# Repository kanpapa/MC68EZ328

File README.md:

# MC68EZ328 DragonOne SBC

We are designing the MC68EZ328 DragonOne SBC with KiCad.

Based on DragonOne V1.0 (C) Khaled Hassounah  
http://www.mediumware.net/DragonOne/DragonOne.htm  

## Spec

* CPU: MC68EZ328 DragonBall-EZ
* Flash Memory: Am29LV033C 32 Megabit (4M x 8-Bit) x 2
* DRAM: MT4LC4M16R6 64 Megabit (4M x 16-bit)
* RTC: DS1306

## Repository Contents

* /b/
  * All b-record for programming and testing the MC68EZ328 DragonOne.
* /bbug/
  * BBUG: a bootstrap mode debugger. Implementation of BBUG using python3 and pyserial.
* /d/
  * This is the data to execute a series of commands in 68k-Monitor.  
* /Hardware/
  * PDF files of schematics and BOMs
* /KiCad/
  * PCB design data and Gerber data for [KiCad](https://www.kicad.org/).
* /Pictues/
  * some pictures
* /src
  * All Source Code for Flash Programming and test programming. The assembler uses [EASy68K](http://www.easy68k.com/).

## How to install uClinux for the DragonOne SBC

[How to install uClinux](/uClinux-build2flash_en.md)  

See below for the uClinux source code and tools for the MC68EZ328 DragonOne SBC.  
https://github.com/kanpapa/uClinux-dist-20020220  
https://github.com/kanpapa/m68k-elf-tools  

## Blog

You can also refer to my blog. (in Japanese)    
https://kanpapa.com/today/electronics/microcomputer/mc68ez328/

## Pictures

MC68EZ328 CPU  

CPU board Rev. 0.3 PCB image  

LAN board Rev. 0.2 PCB image  

Running uClinux  

Running Network!  

## License Information

This code is public domain under the BSD-3-Clause License.  
Copyright (c) 2021, Kazuhiro Ouchi  
All rights reserved.  

References to any products, programs or services do not imply that they will be available in all countries in which their respective owner operates.

Company, product, or services names may be trademarks or services marks of others.

All libraries used in this code are copyright their respective authors.

68k-Monitor Copyright (c) 2015, Hayden Kroepfl

The DragonOne Microcomputer hardware design Copyright (C) Khaled Hassounah

Many thanks to the original authors for making their designs and code avaialble as open source.

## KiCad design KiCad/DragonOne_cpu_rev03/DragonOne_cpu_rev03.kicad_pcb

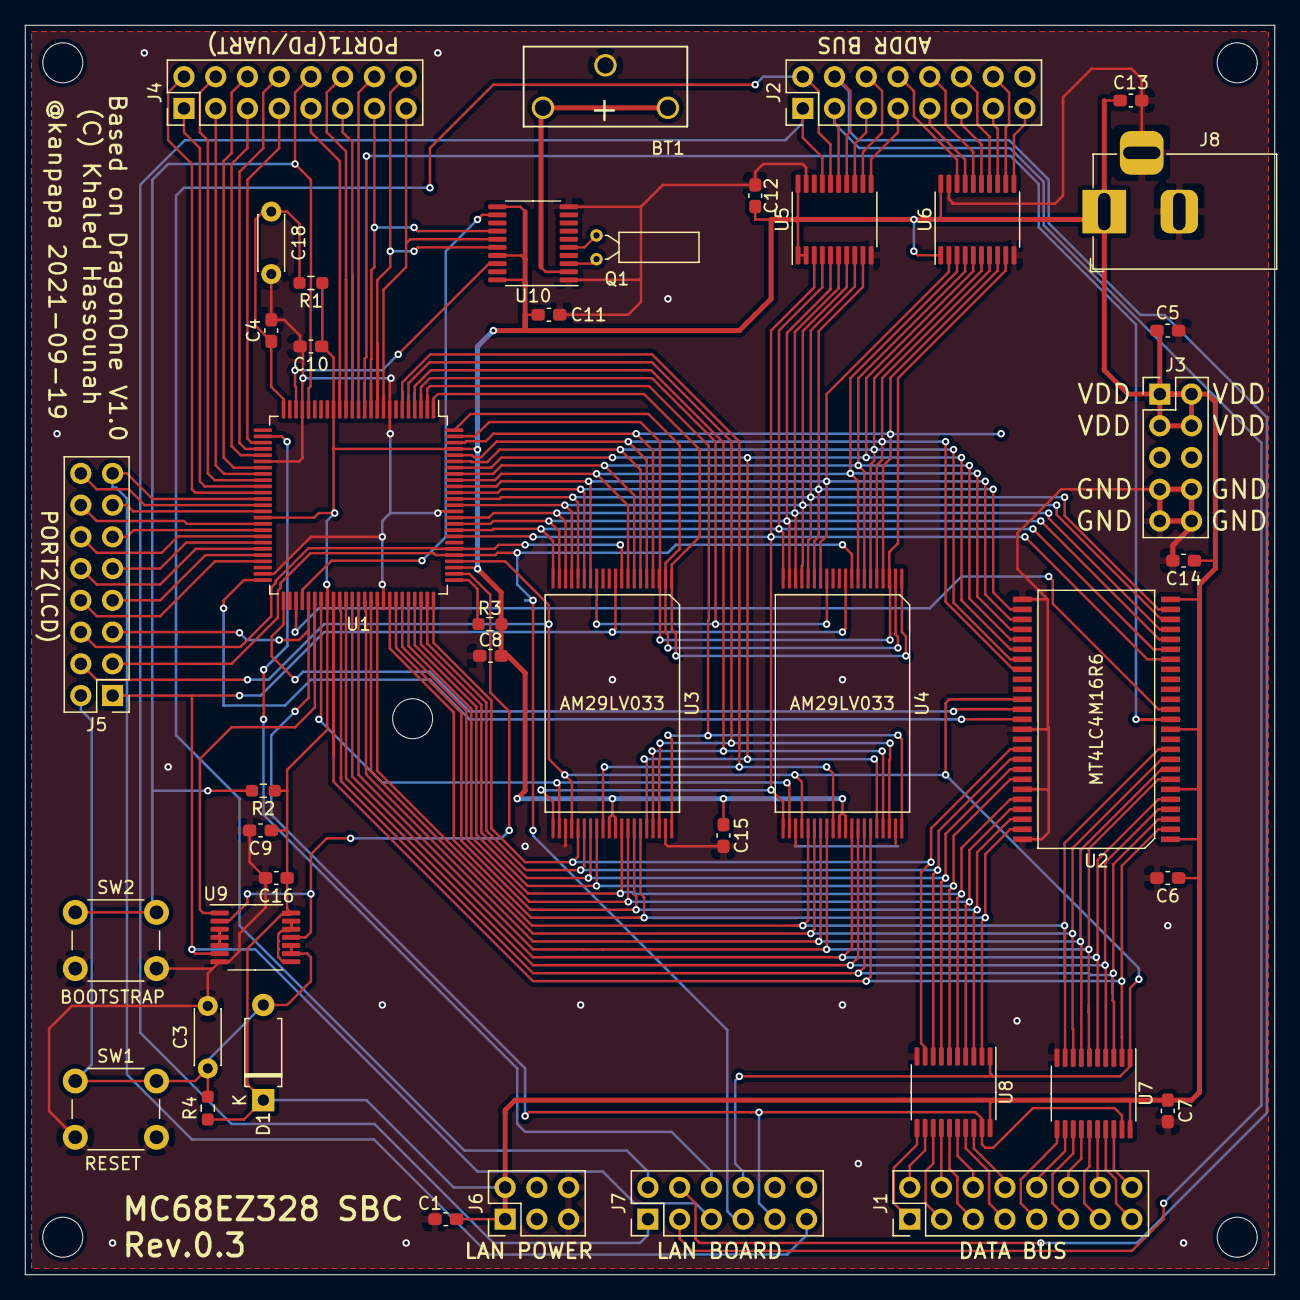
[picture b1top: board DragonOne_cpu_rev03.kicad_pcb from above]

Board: 2 copper layers, 100.0 x 100.0 mm, 48 parts (0 on the bottom side), 120 nets.

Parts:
BT1: 3V; CH74-2032LF
C1, C4, C5, C6, C7, C8, C9, C10, C11, C12, C13, C14, C15, C16: 0.1uf; C_0603_1608Metric_Pad1.08x0.95mm_HandSolder
C3, C18: 2.2uf; C_Disc_D4.3mm_W1.9mm_P5.00mm
D1: 1N4148; D_A-405_P7.62mm_Horizontal
J1: DATA_BUS; PinHeader_2x08_P2.54mm_Vertical
J2: ADDR_BUS; PinHeader_2x08_P2.54mm_Vertical
J3: POWER; PinHeader_2x05_P2.54mm_Vertical
J4: PORT1; PinHeader_2x08_P2.54mm_Vertical
J5: PORT2; PinHeader_2x08_P2.54mm_Vertical
J6: LAN POWER; PinHeader_2x03_P2.54mm_Vertical
J7: LAN CONTROL; PinHeader_2x06_P2.54mm_Vertical
J8: Barrel_Jack_Switch; BarrelJack_Horizontal
MH1, MH2, MH3, MH4, MH5: MountingHole_3.2mm_M3
Q1: 32.768kHz; Crystal_DS26_D2.0mm_L6.0mm_Horizontal
R1: 430; R_0603_1608Metric_Pad0.98x0.95mm_HandSolder
R2, R3: 3.3K; R_0603_1608Metric_Pad0.98x0.95mm_HandSolder
R4: 3.3k; R_0603_1608Metric_Pad0.98x0.95mm_HandSolder
SW1: RESET; SW_PUSH_6mm
SW2: BOOTSTRAP; SW_PUSH_6mm
U1: MC68EZ328; TQFP-100_14x14mm_P0.5mm
U2: MT4LC4M16R6; TSOP-II-50_21x10.16mm_P0.8mm
U3, U4: AM29LV033; TSOP-I-40_18.4x10mm_P0.5mm
U5, U6, U7, U8: 74LCX245; TSSOP-20_4.4x6.5mm_P0.65mm
U9: 74LCX00; TSSOP-14_4.4x5mm_P0.65mm
U10: DS1306; TSSOP-20_4.4x6.5mm_P0.65mm

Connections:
/A1: U1.83, U2.19, U3.21, U4.21, U5.3
/A2: U1.84, U2.20, U3.20, U4.20, U5.4
/A3: U1.85, U2.21, U3.19, U4.19, U5.5
/A4: U1.86, U2.22, U3.18, U4.18, U5.6
/A5: U1.88, U2.23, U3.17, U4.17, U5.7
/A6: U1.89, U2.24, U3.16, U4.16, U5.8
/A7: U1.90, U2.27, U3.15, U4.15, U5.9
/A8: U1.91, U2.28, U3.14, U4.14, U6.2
/A9: U1.92, U2.29, U3.8, U4.8, U6.3
/A10: U1.93, U2.30, U3.7, U4.7, U6.4
/A11: U1.94, U2.31, U3.36, U4.36, U6.5
/A12: U1.95, U2.32, U3.6, U4.6, U6.6
/A13: U1.96, U2.33, U3.5, U4.5, U6.7
/A14: U1.98, U3.4, U4.4, U6.8
/A15: U1.99, U3.3, U4.3, U6.9
/A16: U1.100, U3.2, U4.2
/A17: U1.1, U3.1, U4.1
/A18: U1.2, U3.40, U4.40
/A19: U1.3, U3.13, U4.13
/A20: U1.4, U3.37, U4.37
/A21: U1.5, U3.38, U4.38
/A22: U1.6, U3.29, U4.29
/AB1: J2.1, J7.1, U5.17
/AB2: J2.2, J7.2, U5.16
/AB3: J2.3, J7.3, U5.15
/AB4: J2.4, J7.4, U5.14
/AB5: J2.5, U5.13
/AB6: J2.6, U5.12
/AB7: J2.7, U5.11
/AB8: J2.8, U6.18
/AB9: J2.9, U6.17
/AB10: J2.10, U6.16
/AB11: J2.11, U6.15
/AB12: J2.12, U6.14
/AB13: J2.13, U6.13
/AB14: J2.14, U6.12
/AB15: J2.15, U6.11
/CLOCK: U1.23, U10.18
/D0: U1.75, U2.41, U3.25, U8.9
/D1: U1.74, U2.42, U3.26, U8.8
/D2: U1.73, U2.43, U3.27, U8.7
/D3: U1.72, U2.44, U3.28, U8.6
/D4: U1.71, U2.46, U3.32, U8.5
/D5: U1.70, U2.47, U3.33, U8.4
/D6: U1.69, U2.48, U3.34, U8.3
/D7: U1.68, U2.49, U3.35, U8.2
/D8: U1.66, U2.10, U4.25, U7.9
/D9: U1.65, U2.9, U4.26, U7.8
/D10: U1.64, U2.8, U4.27, U7.7
/D11: U1.63, U2.7, U4.28, U7.6
/D12: U1.62, U2.5, U4.32, U7.5
/D13: U1.61, U2.4, U4.33, U7.4
/D14: U1.60, U2.3, U4.34, U7.3
/D15: U1.59, U2.2, U4.35, U7.2
/DB0: J1.1, U8.11
/DB1: J1.2, U8.12
/DB2: J1.3, U8.13
/DB3: J1.4, U8.14
/DB4: J1.5, U8.15
/DB5: J1.6, U8.16
/DB6: J1.7, U8.17
/DB7: J1.8, U8.18
/DB8: J1.9, U7.11
/DB9: J1.10, U7.12
/DB10: J1.11, U7.13
/DB11: J1.12, U7.14
/DB12: J1.13, U7.15
/DB13: J1.14, U7.16
/DB14: J1.15, U7.17
/DB15: J1.16, U7.18
/LACD: J5.16, U1.38
/LCLK: J5.13, U1.39
/LCON: J5.15, J7.11, U1.37
/LD0: J5.7, U1.46
/LD1: J5.10, U1.45
/LD2: J5.9, U1.44
/LD3: J5.12, U1.43
/LFLM: J5.11, U1.42
/LLP: J5.14, U1.41
/PD0: J4.2, U1.36
/PD1: J4.1, U1.35
/PD2: J4.4, U1.34
/PD3: J4.3, U1.33
/PD4: J4.6, U1.32
/PD5: J4.5, U1.30
/PD6: J4.8, U1.29
/PD7: J4.7, U1.28
/PWM0: J5.8, U1.47
/RXD: J4.14, U1.13
/SCLK: J4.13, U1.11, U10.14
/SRXD: J4.16, U1.10, U10.16
/STXD: J4.15, U1.9, U10.15
/TIME: U1.54, U10.12
/TXD: J4.11, U1.14
/~BDM: J4.10, R2.2, SW2.1, U1.21
/~CAS0: U1.51, U2.37
/~CAS1: U1.50, U2.38
/~CSA0: U1.57, U3.22, U4.22
/~CTS: J4.9, U1.16
/~DWE: U1.12, U2.13
/~EXTRN: J5.5, J7.9, U1.55, U7.19, U8.19
/~IRQ5: J7.6, U1.27
/~LWE: J5.6, U1.81, U3.9
/~PRSET: U1.77, U9.2, U9.11
/~RAS0: U1.53, U2.14
/~RD: J5.4, J7.8, U1.79, U2.36, U3.24, U4.24, U7.1, U8.1
/~RESET: J5.1, J7.5, U3.10, U4.10, U9.6
/~RTS: J4.12, U1.15
/~SRSET: U1.56, U9.1
/~UWE: J5.3, J7.7, U1.80, U4.9
/~XRSET: C3.1, D1.2, J5.2, R4.2, SW1.1, U9.9, U9.10
GND: BT1.2, C1.2, C3.2, C4.2, C5.2, C6.2, C7.2, C8.2, C9.2, C10.2, C11.2, C12.2, C13.2, C14.2, C15.2, C16.2, C18.2, J3.7, J3.8, J3.9, J3.10, J6.5, J6.6, J8.2, J8.3, SW1.2, SW2.2, U1.8, U1.22, U1.31, U1.49, U1.67, U1.87, U2.26, U2.39, U2.45, U2.50, U3.23, U3.39, U4.23, U4.39, U5.10, U5.19, U6.10, U6.19, U7.10, U8.10, U9.7, U10.1, U10.10
unnamed: BT1.1, U10.2
unnamed: C4.1, C18.1, R1.2, U1.25
unnamed: Q1.1, U10.3
unnamed: Q1.2, U10.5
unnamed: R3.2, U1.76
unnamed: U9.3, U9.4, U9.5
unnamed: U9.8, U9.12, U9.13
VDD: C1.1, C5.1, C6.1, C7.1, C8.1, C9.1, C10.1, C11.1, C12.1, C13.1, C14.1, C15.1, C16.1, D1.1, J3.1, J3.2, J3.3, J3.4, J6.1, J6.2, J8.1, R1.1, R2.1, R3.1, R4.1, U1.17, U1.40, U1.58, U1.78, U1.97, U2.1, U2.6, U2.12, U2.25, U3.30, U3.31, U4.30, U4.31, U5.1, U5.2, U5.20, U6.1, U6.20, U7.20, U8.20, U9.14, U10.11, U10.17, U10.20

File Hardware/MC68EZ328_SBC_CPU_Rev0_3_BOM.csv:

Reference,Quantity,Value,Footprint,販売店（参考）,型番,URL,備考
BT1,1,3V,DragonOne_rev00:CH74-2032LF,秋月電子,ボタン電池基板取付用ホルダーＣＲ２０３２用（縦・小型）[CH74-2032LF][P-01443]1個 ￥50(税込),https://akizukidenshi.com/catalog/g/gP-01443/,
C3 C18,2,2.2uf,Capacitor_THT:C_Disc_D4.3mm_W1.9mm_P5.00mm,秋月電子,積層セラミックコンデンサー２．２μＦ５０Ｖ　Ｘ７Ｒ　５ｍｍ[RDER71H225K2K1H03B][P-08152]1個 ￥25(税込),https://akizukidenshi.com/catalog/g/gP-08152/,
C1 C4 C5 C6 C7 C8 C9 C10 C11 C12 C13 C14 C15 C16,14,0.1uf,Capacitor_SMD:C_0603_1608Metric_Pad1.08x0.95mm_HandSolder,秋月電子,太陽誘電チップ積層セラミックコンデンサー０．１μＦ２５Ｖ　Ｆ／Ｙ５Ｖ　１６０８　（１００個入）[TMK107F104ZZ-T][P-13071]1パック ￥100,https://www.akizukidenshi.com/catalog/g/gP-13071/,
D1,1,1N4148,Diode_THT:D_A-405_P10.16mm_Horizontal,秋月電子,汎用小信号高速スイッチング・ダイオード１Ｎ４１４８　１００Ｖ２００ｍＡ（５０本入）[1N4148][I-00941]1パック ￥100(税込),https://akizukidenshi.com/catalog/g/gI-00941/,
J1,1,DATA_BUS,Connector_PinHeader_2.54mm:PinHeader_2x08_P2.54mm_Vertical,秋月電子,ピンヘッダ２×８,https://akizukidenshi.com/catalog/g/gC-00082/,"ピンヘッダ２×４０（８０Ｐ）[PH-2x40SG][C-00082]1本￥50(税込)を折って使う"
J2,1,ADDR_BUS,Connector_PinHeader_2.54mm:PinHeader_2x08_P2.54mm_Vertical,秋月電子,ピンヘッダ２×８,,
J3,1,POWER,Connector_PinHeader_2.54mm:PinHeader_2x05_P2.54mm_Vertical,秋月電子,ピンヘッダ２×５,,
J4,1,PORT1,Connector_PinHeader_2.54mm:PinHeader_2x08_P2.54mm_Vertical,秋月電子,ピンヘッダ２×８,,
J5,1,PORT2,Connector_PinHeader_2.54mm:PinHeader_2x08_P2.54mm_Vertical,秋月電子,ピンヘッダ２×８,,
J6,1,LAN POWER,Connector_PinHeader_2.54mm:PinHeader_2x03_P2.54mm_Vertical,秋月電子,ピンヘッダ２×３,,
J7,1,LAN BOARD,Connector_PinHeader_2.54mm:PinHeader_2x06_P2.54mm_Vertical,秋月電子,ピンヘッダ２×６,,
J8,1,POWER,Cobbector_BarrelJack:BarrelJack_Horizontal,秋月電子,２．１ｍｍ標準ＤＣジャック基板取付用　ＭＪ－１７９Ｐ[MJ-179P][C-00077]1個 ￥40(税込),https://www.akizukidenshi.com/catalog/g/gC-00077/,
Q1,1,32.768kHz,Crystal:Crystal_AT310_D3.0mm_L10.0mm_Horizontal,秋月電子,"クリスタル（水晶発振子）32.768KHz[VT-200-F 32.768kHz][P-04005]1個 ￥30(税込)",https://akizukidenshi.com/catalog/g/gP-04005/,
R1,1,430Ω,Resistor_SMD:R_0603_1608Metric_Pad0.98x0.95mm_HandSolder,"千石電商日米商事共立エレショップ",チップ抵抗１／１０Ｗ４３０Ω ０６０３ １６０８,,
R2 R3 R4,3,3.3K,Resistor_SMD:R_0603_1608Metric_Pad0.98x0.95mm_HandSolder,"千石電商日米商事秋月電子共立エレショップ",チップ抵抗１／１０Ｗ３．３ｋΩ　０６０３　１６０８,https://www.akizukidenshi.com/catalog/g/gR-14661/,
SW1,1,RESET,Button_Switch_THT:SW_PUSH_6mm,秋月電子,タクトスイッチ（オレンジ色）[TS-0606-F-N-ORG][P-03652]1個 ￥10(税込),https://akizukidenshi.com/catalog/g/gP-03652/,
SW2,1,BOOTSTRAP,Button_Switch_THT:SW_PUSH_6mm,秋月電子,タクトスイッチ（白色）[TS-0606-F-N-WHT][P-03648]1個 ￥10(税込),https://akizukidenshi.com/catalog/g/gP-03648/,色はおこのみで
U1,1,MC68EZ328,Package_QFP:TQFP-100_14x14mm_P0.5mm,AliExpress、eBay,,,
U10,1,DS1306,Package_SO:TSSOP-20_4.4x6.5mm_P0.65mm,AliExpress、eBay,,,
U2,1,MT4LC4M16R6,DragonOne_rev00:TSOP-II-50_21x10.16mm_P0.8mm,AliExpress、eBay,,,
U3 U4,2,AM29LV033,DragonOne_rev00:TSOP-I-40_18.4x10mm_P0.5mm,AliExpress、eBay,,,
U5 U6 U7 U8,4,74LCX245,Package_SO:TSSOP-20_4.4x6.5mm_P0.65mm,秋月電子,８ビットバストランシーバ３ステート出力７４ＬＣＸ２４５ＦＴ（５個入）[74LCX245FT(AJ)][I-14111]1パック ￥130(税込),https://akizukidenshi.com/catalog/g/gI-14111/,
U9,1,74LCX00,Package_SO:TSSOP-14_4.4x5mm_P0.65mm,秋月電子,４回路２入力ＮＡＮＤ７４ＬＣＸ００ＦＴ（５個入）[74LCX00FT(AJ)][I-14106]1パック ￥100(税込),https://akizukidenshi.com/catalog/g/gI-14106/,

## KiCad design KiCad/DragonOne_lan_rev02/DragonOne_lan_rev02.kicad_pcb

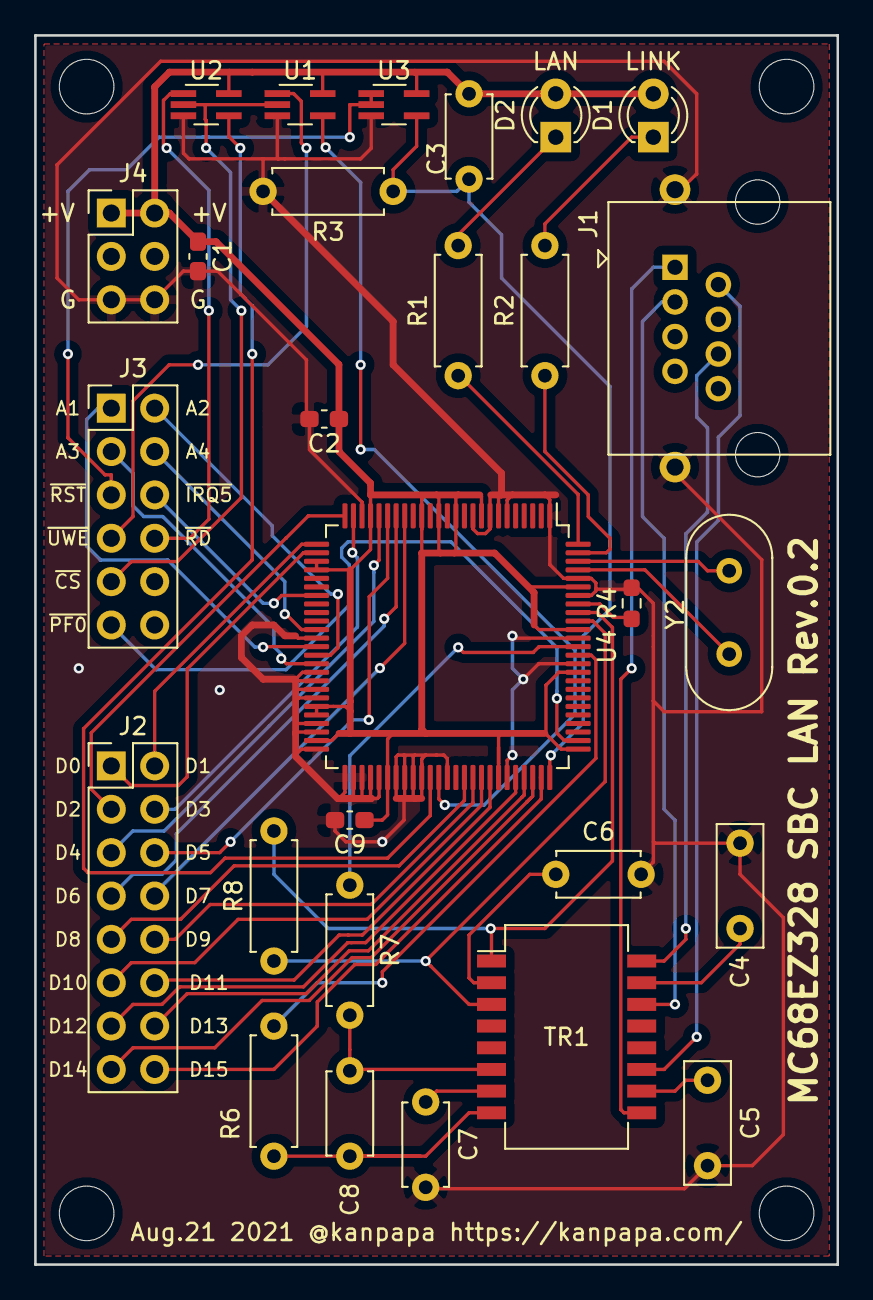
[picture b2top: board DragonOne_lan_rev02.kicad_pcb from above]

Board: 2 copper layers, 47.0 x 72.0 mm, 32 parts (0 on the bottom side), 52 nets.

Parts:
C1, C2, C9: 0.1uF; C_0603_1608Metric_Pad1.08x0.95mm_HandSolder
C3, C6, C7: 0.1uF; C_Disc_D4.7mm_W2.5mm_P5.00mm
C4: 4700pF/1kV; C_Disc_D7.0mm_W2.5mm_P5.00mm
C5: 4700pF/1KV; C_Disc_D7.0mm_W2.5mm_P5.00mm
C8: 560pF; C_Disc_D4.7mm_W2.5mm_P5.00mm
D1: LINK LED; LED_D3.0mm
D2: LAN LED; LED_D3.0mm
J1: 8P8C_Shielded; RJ45_Akizuki_7810-8P8C
J2: DATA_BUS; PinHeader_2x08_P2.54mm_Vertical
J3: CTRL_BUS; PinHeader_2x06_P2.54mm_Vertical
J4: PWR; PinHeader_2x03_P2.54mm_Vertical
MH1, MH2, MH3, MH4: MountingHole_3.2mm_M3
R1, R2: 560; R_Axial_DIN0207_L6.3mm_D2.5mm_P7.62mm_Horizontal
R3: 100K; R_Axial_DIN0207_L6.3mm_D2.5mm_P7.62mm_Horizontal
R4: 4.99K 1%; R_0603_1608Metric_Pad0.98x0.95mm_HandSolder
R6, R7: 8.2 1%; R_Axial_DIN0207_L6.3mm_D2.5mm_P7.62mm_Horizontal
R8: 100, 1%; R_Axial_DIN0207_L6.3mm_D2.5mm_P7.62mm_Horizontal
TR1: E2023EL; Transformer_Ethernet_Bourns_PT61017PEL
U1, U2: TC7S32FU; SOT-353_SC-70-5_Handsoldering
U3: TC7SH00FU; SOT-353_SC-70-5_Handsoldering
U4: CS8900A-CQ3Z; TQFP-100_14x14mm_P0.5mm
Y2: 20MHz; Crystal_HC49-4H_Vertical

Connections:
/AB1: J3.1, U4.38
/AB2: J3.2, U4.39
/AB3: J3.3, U4.40
/AB4: J3.4, U4.36
/DB0: J2.1, U4.27
/DB1: J2.2, U4.26
/DB2: J2.3, U4.25
/DB3: J2.4, U4.24
/DB4: J2.5, U4.21
/DB5: J2.6, U4.20
/DB6: J2.7, U4.19
/DB7: J2.8, U4.18
/DB8: J2.9, U4.65
/DB9: J2.10, U4.66
/DB10: J2.11, U4.67
/DB11: J2.12, U4.68
/DB12: J2.13, U4.71
/DB13: J2.14, U4.72
/DB14: J2.15, U4.73
/DB15: J2.16, U4.74
/PF0: J3.11, U4.77
/RD+: J1.3, TR1.14
/RD-: J1.6, TR1.16
/RXD+: R8.1, TR1.3, U4.91
/RXD-: R8.2, TR1.1, U4.92
/TD+: J1.1, TR1.9
/TD-: J1.2, TR1.11
/TXD+: C8.1, R6.2, TR1.8
/TXD-: C8.2, R7.2, TR1.6
/~CSB0: J3.9, U1.2, U2.2
/~IRQ5: J3.6, U4.32
/~RD: J3.8, U2.1
/~RESET: J3.5, U3.1, U3.2
/~UWE: J3.7, U1.1
GND: C1.2, C2.2, C4.2, C5.2, C6.2, C7.2, C9.2, J1.SH, J4.5, J4.6, R3.2, R4.2, U1.3, U2.3, U3.3, U4.1, U4.6, U4.7, U4.8, U4.10, U4.23, U4.37, U4.41, U4.42, U4.43, U4.44, U4.47, U4.48, U4.50, U4.51, U4.52, U4.53, U4.54, U4.55, U4.57, U4.58, U4.59, U4.60, U4.63, U4.70, U4.86, U4.89, U4.94, U4.96
unnamed: C3.2, R3.1, U3.4, U4.75
unnamed: C4.1, TR1.15
unnamed: C5.1, TR1.10
unnamed: C6.1, TR1.2
unnamed: C7.1, TR1.7
unnamed: D1.1, R2.2
unnamed: D2.1, R1.2
unnamed: R1.1, U4.100
unnamed: R2.1, U4.99
unnamed: R4.1, U4.93
unnamed: R6.1, U4.87
unnamed: R7.1, U4.88
unnamed: U1.4, U4.62
unnamed: U2.4, U4.61
unnamed: U4.97, Y2.2
unnamed: U4.98, Y2.1
VCC: C1.1, C2.1, C3.1, C9.1, D1.2, D2.2, J4.1, J4.2, U1.5, U2.5, U3.5, U4.9, U4.12, U4.14, U4.16, U4.22, U4.28, U4.29, U4.45, U4.46, U4.49, U4.56, U4.69, U4.76, U4.85, U4.90, U4.95

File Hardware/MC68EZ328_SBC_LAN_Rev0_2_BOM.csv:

Reference,Quantity,Value,販売店（参考）,型番,URL,備考
C1 C2 C9,3,0.1uF,秋月電子,太陽誘電チップ積層セラミックコンデンサー０．１μＦ２５Ｖ　Ｆ／Ｙ５Ｖ　１６０８　（１００個入）[TMK107F104ZZ-T][P-13071]1パック ￥100(税込),https://akizukidenshi.com/catalog/g/gP-13071/,
C4 C5,2,4700pF/1kV,マルツ,セラミックコンデンサー 4700pF【CY5P472K1K12D】パッケージ：・静電容量：4700pF・定格電圧：1kVDC・容量許容差：±10％・リードピッチ：5mm,https://www.marutsu.co.jp/GoodsDetail.jsp?q=CY5P472K&salesGo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,
C3 C6 C7,3,0.1uF,秋月電子,"リード型積層セラミックコンデンサー０．１μＦ５０Ｖ　Ｆ　５ｍｍピッチ　（１０個入）[RPEF11H104Z2M1A01A][P-00340]1テープ ￥100(税込)",https://akizukidenshi.com/catalog/g/gP-00340/,
C8,1,560pF,秋月電子,"絶縁ラジアルリード型積層セラミックコンデンサー５６０ｐＦ５０Ｖ５ｍｍ（１０個入）[RDE5C1H561J0K1H03B][P-08111]1パック ￥100(税込)",https://akizukidenshi.com/catalog/g/gP-08111/,
D1,1,LINK LED,aitendo,,,
D2,1,LAN LED,aitendo,,,
IC1,1,CS8900A-CQ3Z,AliExpress,,,
J1,1,LAN_CON,秋月電子,基板取付用ＬＡＮコネクタ（モジュラージャック）（ＲＪ－４５）[7810-8P8C][C-00159]1個 ￥100(税込),https://akizukidenshi.com/catalog/g/gC-00159/,
J2,1,DATA_BUS,秋月電子,ピンヘッダ２×４０（８０Ｐ）[PH-2x40SG][C-00082]1本 ￥50(税込),https://akizukidenshi.com/catalog/g/gC-00082/,折って使う
J3,1,CTRL_BUS,秋月電子,ピンヘッダ２×４０（８０Ｐ）[PH-2x40SG][C-00082]1本 ￥50(税込),https://akizukidenshi.com/catalog/g/gC-00082/,折って使う
J4,1,PWR,秋月電子,ピンヘッダ２×３（６Ｐ）[PH-2x3SG][C-15825]1本 ￥10(税込) 数割有,https://akizukidenshi.com/catalog/g/gC-15825/,
R1 R2,2,560Ω,千石電商,カーボン抵抗 1/4W 560Ω±5% RD25J 560Ω,,
R3,1,100K,千石電商,カーボン抵抗 1/4W 100KΩ±5% RD25J 100KΩ,,
R4,1,4.99K 1%,秋月電子,"超精密級 金属皮膜チップ抵抗器　１６０８　１／１０Ｗ４．９９ｋΩ０．１％（５個入）[RG1608N-4991B-T5][R-11794]1パック ￥100(税込)",https://akizukidenshi.com/catalog/g/gR-11794/,
R6 R7,2,8.2 1%,千石電商,金属被膜抵抗器 1/4W 8.2Ω±1% RLC25FX 8.2Ω,,
R8,1,"100, 1%",千石電商,金属被膜抵抗器 1/4W 100Ω±1% RLC25FY 100Ω,,
TR1,1,E2023EL,"マルツ, AliExpress",,,
U1 U2,2,TC7S32FU,秋月電子,２入力ＯＲゲートＴＣ７Ｓ３２ＦＵ（５個入）[TC7S32FU][I-10465]1パック ￥150(税込),https://akizukidenshi.com/catalog/g/gI-10465/,
U3,1,TC7SH00FU,秋月電子,２入力ＮＡＮＤ ＴＣ７ＳＨ００ＦＵ（１０個入）[TC7SH00FULJ(CB][I-15748]1パック ￥100(税込),https://akizukidenshi.com/catalog/g/gI-15748/,
Y2,1,20MHz,秋月電子,クリスタル（水晶発振子）２０ＭＨｚ[HUSG-20.000-20][P-08673]1個 ￥30(税込),https://akizukidenshi.com/catalog/g/gP-08673/,

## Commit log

2021-03-16 1st commit
2021-03-16 Added spec
2021-03-16 Update spec
2021-03-20 Added 2flash-kh and pictures
2021-03-20 Added DragonOne Site URL
2021-03-20 Added CR
2021-03-20 Added pictures
2021-03-20 Added bbug teraterm macro version
2021-03-20 Update bbug
2021-04-10 Fixed for my development environment.
2021-04-10 Added usage in Japanese.
2021-04-10 Fixed typo
2021-04-14 Added repository contents
2021-04-19 Added mdisp.ttl
2021-04-21 1st release
2021-04-22 update indent
2021-04-22 Added initb.py
2021-04-23 Added loadb, start
2021-04-24 Fixed bug
2021-04-24 Updated serialport for macos
2021-04-24 Added schematic
2021-04-25 Updated schematic
2021-04-25 Updated contents list
2021-05-01 Added init.b
2021-05-01 Fixed blank
2021-05-01 Added init.py
2021-05-01 Added stob.py
2021-05-02 Added Monitor.b
2021-05-02 Updated LF code
2021-05-02 Added helloworld.x68
2021-05-02 Added helloworld
2021-05-02 Added echoback
2021-05-03 Updated 32bit address display
2021-05-03 Added flashtools alpha
2021-05-04 Added gitignore
2021-05-04 Updated flashtools src
2021-05-04 Update flashtools
2021-05-05 Update flashtools alpha (erase and program, reset)
2021-05-06 Updated flashtools.x68
2021-05-06 updated flashtools
2021-05-06 Updated flashtools beta version
2021-05-08 Added flashtools_monitor.b
2021-05-08 Fixed line end code
2021-05-08 Fixed S3 address
2021-05-08 Added license information
2021-05-08 Create LICENSE
2021-05-08 Added a monitor program that runs on flash memory
2021-05-08 Added a monitor program that runs on DRAM
2021-05-08 Added B record of monitor program running on DRAM
2021-05-08 Add description for B record
2021-05-08 Update the description of the B record.
2021-05-09 Added stod utility
2021-05-09 Updated hardware spec
2021-05-09 Fixed Spec
2021-05-12 Added btod.py
2021-05-16 Added uClinux-dist patch
2021-05-16 Updated README.md for b
2021-05-16 Fixed crlf code
2021-05-17 Added COPYING
2021-05-21 Added ucsimm sample boot log
2021-05-22 Added memory.c
2021-05-23 Updated Monitor_flashtool_dram
2021-05-23 Updated Monitor_flashtool_dram.b
2021-05-27 Added dtobin.py
2021-05-27 updated dtobin.py
2021-06-08 Added uClinux applications
2021-07-23 Added bin2b.py
2021-07-24 Added toolchain for m68k
2021-07-24 Added uClinux build to flash markdown document
2021-07-24 Updated uClinux-build2flash
2021-07-24 Added Monitor_flashtool_dram_nostart
2021-07-24 Updated url for git clone
2021-07-24 The operation procedure of the monitor was added.
2021-07-25 説明を追加
2021-07-25 m68k toolchainのリポジトリを変更
2021-07-25 Added hardware check programs
2021-08-01 Added cs8900 check program
2021-08-03 Added cs8900a check program
2021-08-06 Added schematics for LAN board
2021-08-16 Added DS1306 test program
2021-08-21 Updated CE signal
2021-08-22 Added DS1306 Sample program
2021-08-22 Updated SPI sample program for DS1306
2021-08-22 Added RTC DS1306 dump program
2021-08-22 Added D file ds1306_readrtc
2021-08-22 Added RTC CS check program
2021-09-05 Added LAN board Rev0.2
2021-09-20 Added KiCad files
2021-09-20 Added BOM for MC68EZ328 SBC Rev0.3
2021-09-20 Added schematic for DragonOne SBC Rev. 0.3
2021-09-20 Added How to install the uClinux
2021-09-20 Updated uClinux install manual
2021-09-27 Added uClinux 2.4.17-uc0 #3 22 Aug 2021 04:05:22
2021-09-27 Renamed uclinux image
2021-12-27 Update uClinux-build2flash_en.md
    Updated debian version.
2021-12-27 Update uClinux-build2flash.md
    Updated debian version
2021-12-27 Update uClinux-build2flash_en.md
    Updated debian version
2024-02-24 Added CSV file
2024-02-24 Changed tsv to csv and file name.
2024-02-24 Fixed filenames
2024-02-24 Update PCB images

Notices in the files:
KiCad/DragonOne_cpu_rev03/DragonOne_cpu_rev03.kicad_pcb:
Copyright Khaled Hassounah
